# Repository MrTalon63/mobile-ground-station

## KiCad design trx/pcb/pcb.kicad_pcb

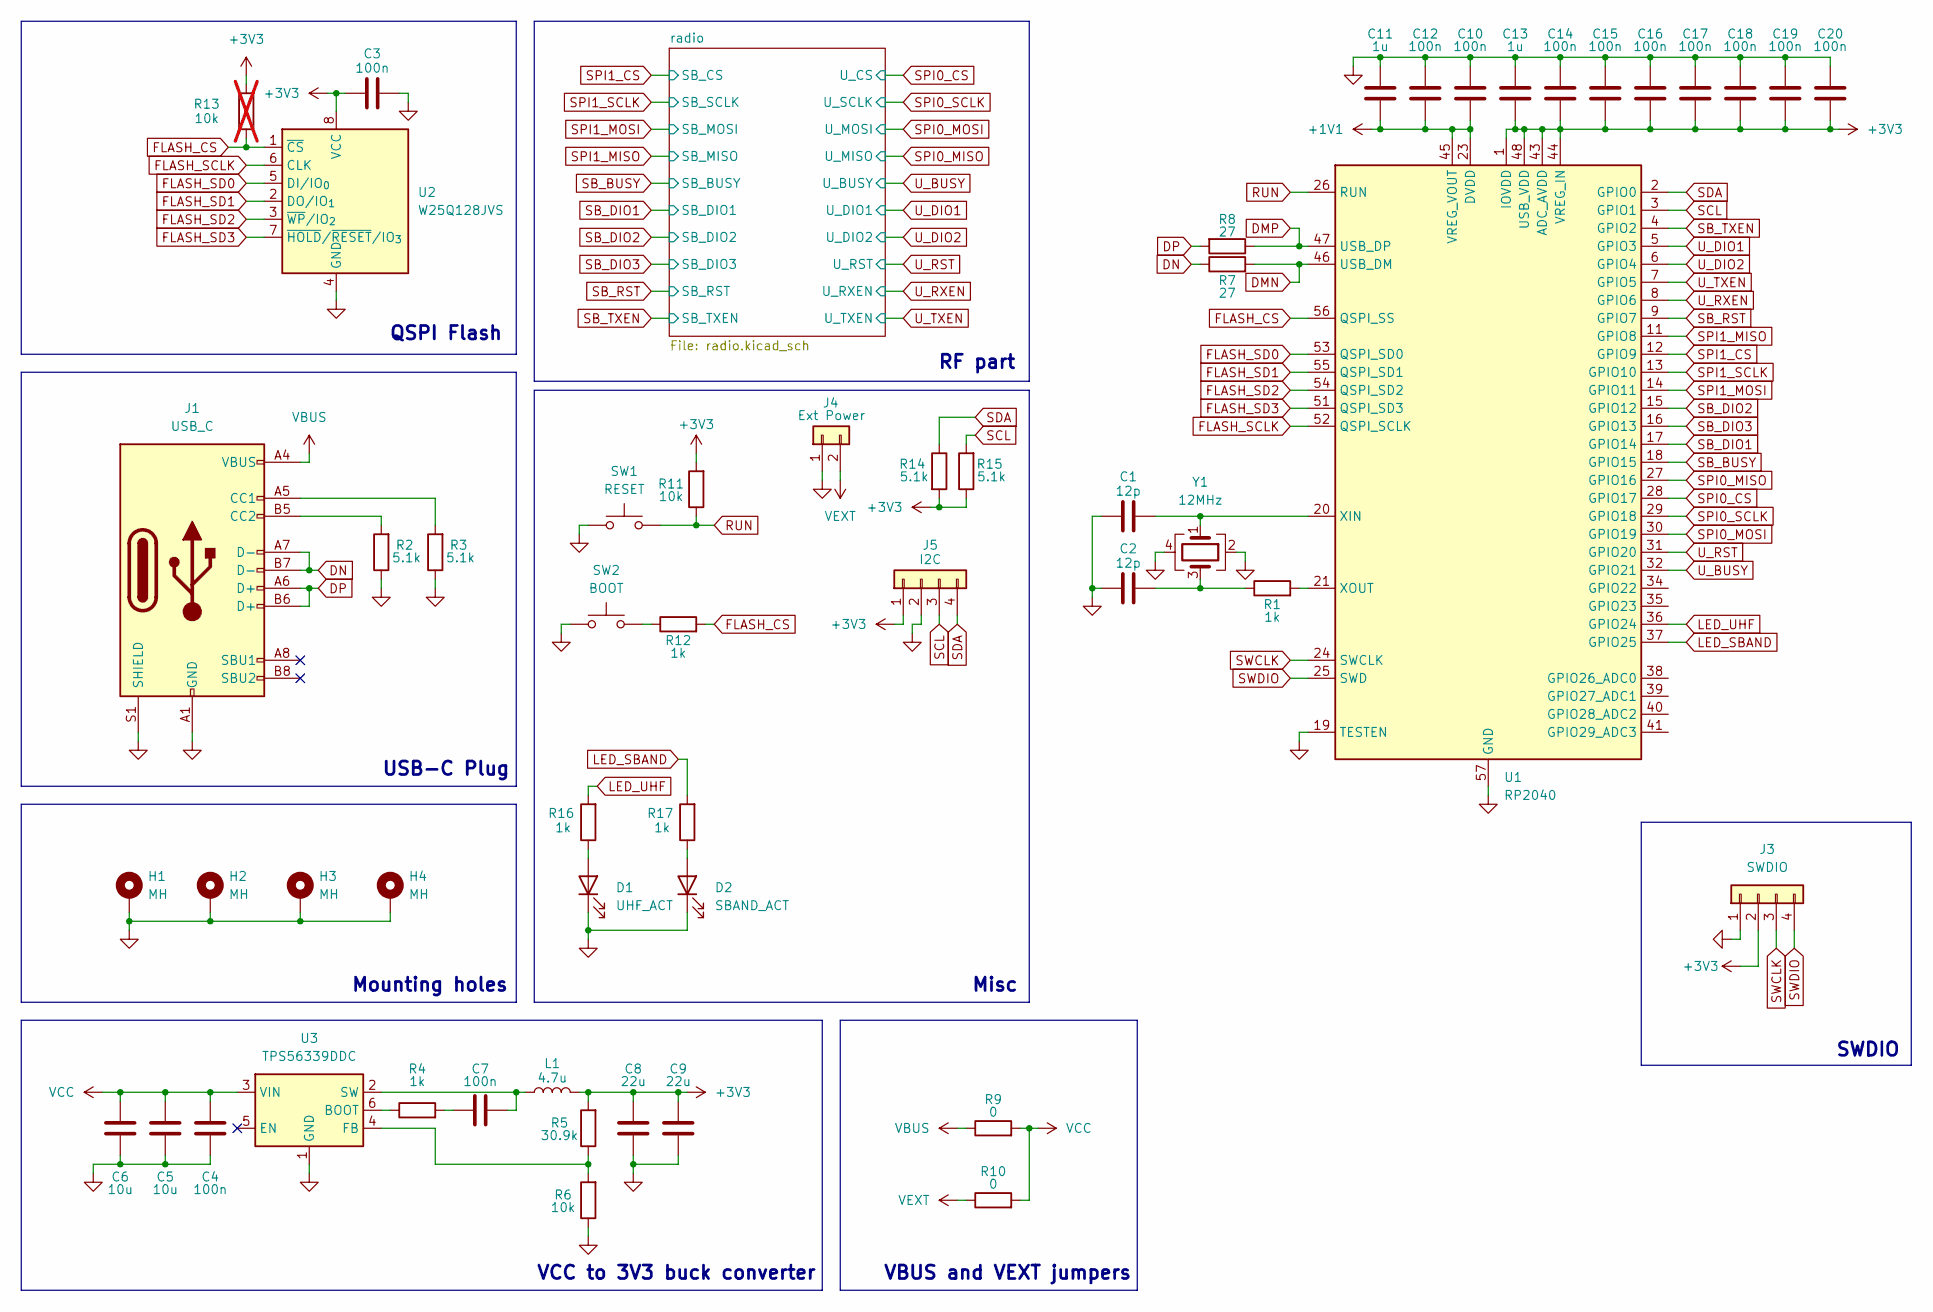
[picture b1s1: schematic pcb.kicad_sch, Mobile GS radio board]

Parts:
C1, C2: 12p; C_0603_1608Metric_Pad1.08x0.95mm_HandSolder
C3, C4, C7, C10, C12, C14, C15, C16, C17, C18, C19, C20: 100n; C_0603_1608Metric_Pad1.08x0.95mm_HandSolder
C5, C6: 10u; C_0603_1608Metric_Pad1.08x0.95mm_HandSolder
C8, C9: 22u; C_0603_1608Metric_Pad1.08x0.95mm_HandSolder
C11, C13: 1u; C_0603_1608Metric_Pad1.08x0.95mm_HandSolder
D1: UHF_ACT; LED_0805_2012Metric_Pad1.15x1.40mm_HandSolder
D2: SBAND_ACT; LED_0805_2012Metric_Pad1.15x1.40mm_HandSolder
H1, H2, H3, H4: MH; MountingHole_2.7mm_M2.5_Pad
J1: USB_C; USB_C_Receptacle_GCT_USB4105-xx-A_16P_TopMnt_Horizontal
J3: SWDIO; PinHeader_1x04_P2.54mm_Vertical
J4: Ext Power; PinSocket_1x02_P2.54mm_Vertical
J5: I2C; PinHeader_1x04_P2.54mm_Vertical
L1: 4.7u; L_Vishay_IHLP-2525
R1, R4, R12, R16, R17: 1k; R_0603_1608Metric_Pad0.98x0.95mm_HandSolder
R2, R3, R14, R15: 5.1k; R_0603_1608Metric_Pad0.98x0.95mm_HandSolder
R5: 30.9k; R_0603_1608Metric_Pad0.98x0.95mm_HandSolder
R6, R11: 10k; R_0603_1608Metric_Pad0.98x0.95mm_HandSolder
R7, R8: 27; R_0603_1608Metric_Pad0.98x0.95mm_HandSolder
R9, R10: 0; R_0805_2012Metric_Pad1.20x1.40mm_HandSolder
R13: 10k; R_0603_1608Metric_Pad0.98x0.95mm_HandSolder; not fitted
SW1: RESET; SW_Push_1P1T_NO_CK_KSC6xxJ
SW2: BOOT; SW_Push_1P1T_NO_CK_KSC6xxJ
U1: RP2040; QFN-56-1EP_7x7mm_P0.4mm_EP3.2x3.2mm
U2: W25Q128JVS; SOIC-8_5.3x5.3mm_P1.27mm
U3: TPS56339DDC; SOT-23-6
Y1: 12MHz; Crystal_SMD_Abracon_ABM3B-4Pin_5.0x3.2mm

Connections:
+1V1: C10.2, C11.2, C12.2, U1.23 (DVDD), U1.45 (VREG_VOUT), U1.50 (DVDD)
+3V3: C3.1, C8.2, C9.2, C13.2, C14.2, C15.2, C16.2, C17.2, C18.2, C19.2, C20.2, J3.2, J5.1, L1.2, R5.2, R11.2, R13.2, R14.2, R15.1, U1.1 (IOVDD), U1.10 (IOVDD), U1.22 (IOVDD), U1.33 (IOVDD), U1.42 (IOVDD), U1.43 (ADC_AVDD), U1.44 (VREG_IN), U1.48 (USB_VDD), U1.49 (IOVDD), U2.8 (VCC); also elsewhere on the board
DMN: R7.2, U1.46 (USB_DM)
DMP: R8.1, U1.47 (USB_DP)
DN: J1.A7 (D-), J1.B7 (D-), R7.1
DP: J1.A6 (D+), J1.B6 (D+), R8.2
FLASH_CS: R12.2, R13.1, U1.56 (QSPI_SS), U2.1 (~CS)
FLASH_SCLK: U1.52 (QSPI_SCLK), U2.6 (CLK)
FLASH_SD0: U1.53 (QSPI_SD0), U2.5 (DI/IO_{0})
FLASH_SD1: U1.55 (QSPI_SD1), U2.2 (DO/IO_{1})
FLASH_SD2: U1.54 (QSPI_SD2), U2.3 (~WP/IO_{2})
FLASH_SD3: U1.51 (QSPI_SD3), U2.7 (~HOLD/~RESET/IO_{3})
GND: C1.1, C2.1, C3.2, C4.1, C5.1, C6.1, C8.1, C9.1, C10.1, C11.1, C12.1, C13.1, C14.1, C15.1, C16.1, C17.1, C18.1, C19.1, C20.1, D1.1 (K), D2.1 (K), H1.1, H2.1, H3.1, H4.1, J1.A1 (GND), J1.A12 (GND), J1.B1 (GND), J1.B12 (GND), J1.S1 (SHIELD), J3.1, J4.1, J5.2, R2.1, R3.1, R6.1, SW1.1, SW2.1, U1.19 (TESTEN), U1.57 (GND), U2.4 (GND), U3.1 (GND), Y1.2, Y1.4; also elsewhere on the board
LED_SBAND: R17.2, U1.37 (GPIO25)
LED_UHF: R16.2, U1.36 (GPIO24)
unnamed: C2.2, R1.1, Y1.3
unnamed: C7.2, R4.2
unnamed: D1.2 (A), R16.1
unnamed: D2.2 (A), R17.1
unnamed: J1.A5 (CC1), R3.2
unnamed: J1.B5 (CC2), R2.2
unnamed: R12.1, SW2.2
unnamed: C1.2, U1.20 (XIN), Y1.1
unnamed: R1.2, U1.21 (XOUT)
unnamed: R4.1, U3.6 (BOOT)
unnamed: R5.1, R6.2, U3.4 (FB)
unnamed: C7.1, L1.1, U3.2 (SW)
RUN: R11.1, SW1.2, U1.26 (RUN)
SB_BUSY: U1.18 (GPIO15); also elsewhere on the board
SB_DIO1: U1.17 (GPIO14); also elsewhere on the board
SB_DIO2: U1.15 (GPIO12); also elsewhere on the board
SB_DIO3: U1.16 (GPIO13); also elsewhere on the board
SB_RST: U1.9 (GPIO7); also elsewhere on the board
SB_TXEN: U1.4 (GPIO2); also elsewhere on the board
SCL: J5.3, R15.2, U1.3 (GPIO1)
SDA: J5.4, R14.1, U1.2 (GPIO0)
SPI0_CS: U1.28 (GPIO17); also elsewhere on the board
SPI0_MISO: U1.27 (GPIO16); also elsewhere on the board
SPI0_MOSI: U1.30 (GPIO19); also elsewhere on the board
SPI0_SCLK: U1.29 (GPIO18); also elsewhere on the board
SPI1_CS: U1.12 (GPIO9); also elsewhere on the board
SPI1_MISO: U1.11 (GPIO8); also elsewhere on the board
SPI1_MOSI: U1.14 (GPIO11); also elsewhere on the board
SPI1_SCLK: U1.13 (GPIO10); also elsewhere on the board
SWCLK: J3.3, U1.24 (SWCLK)
SWDIO: J3.4, U1.25 (SWD)
U_BUSY: U1.32 (GPIO21); also elsewhere on the board
U_DIO1: U1.5 (GPIO3); also elsewhere on the board
U_DIO2: U1.6 (GPIO4); also elsewhere on the board
U_RST: U1.31 (GPIO20); also elsewhere on the board
U_RXEN: U1.8 (GPIO6); also elsewhere on the board
U_TXEN: U1.7 (GPIO5); also elsewhere on the board
VBUS: J1.A4 (VBUS), J1.A9 (VBUS), J1.B4 (VBUS), J1.B9 (VBUS), R9.1
VCC: C4.2, C5.2, C6.2, R9.2, R10.2, U3.3 (VIN)
VEXT: J4.2, R10.1

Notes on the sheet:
QSPI Flash
Misc
VBUS and VEXT jumpers
RF part
Mounting holes
USB-C Plug
SWDIO
VCC to 3V3 buck converter

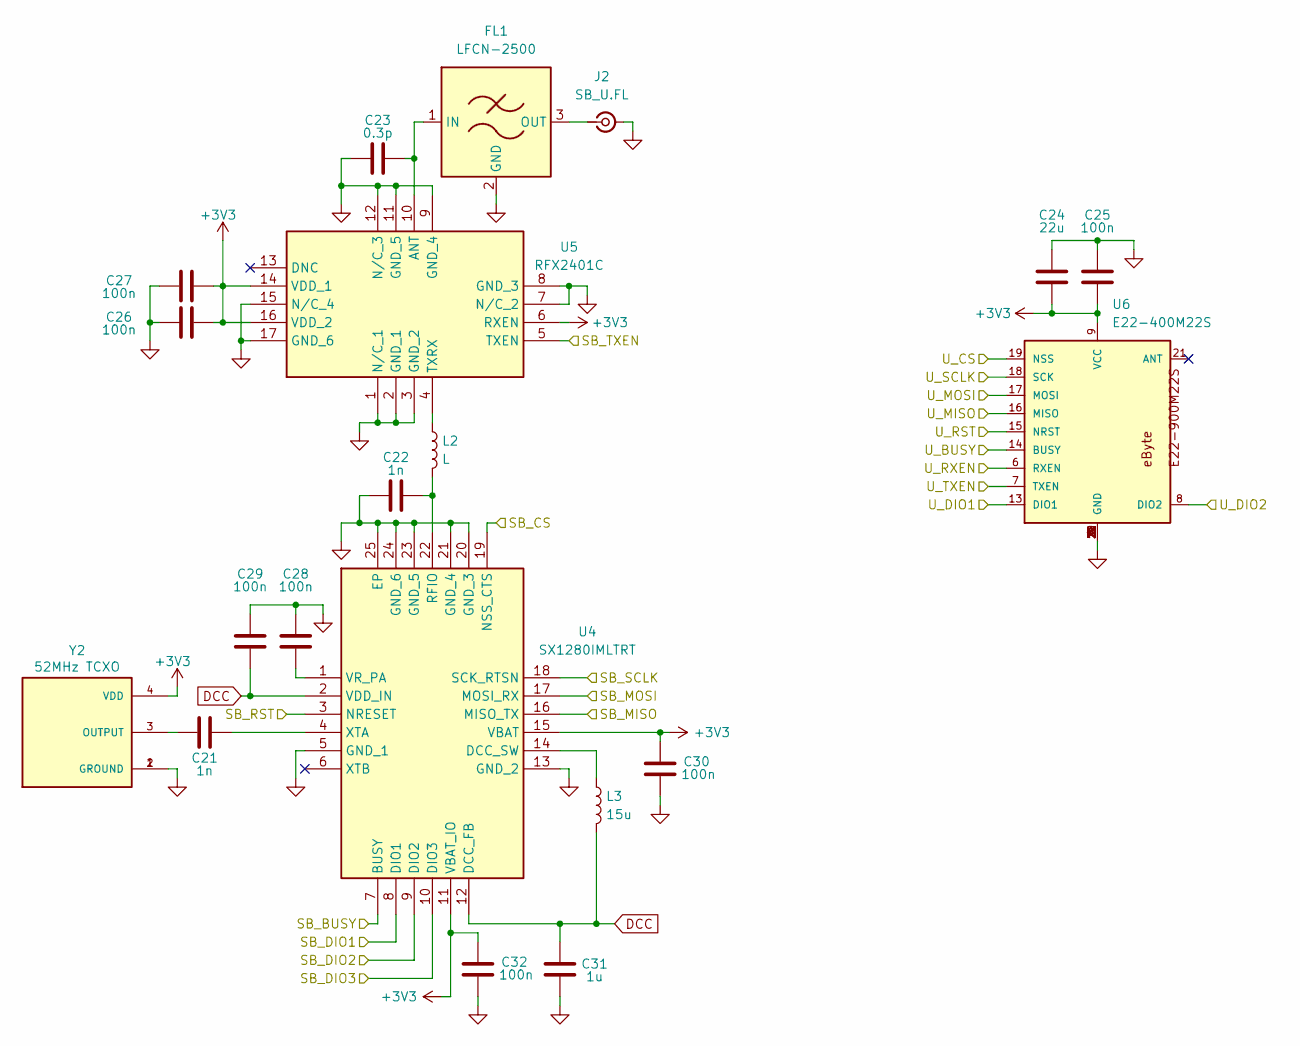
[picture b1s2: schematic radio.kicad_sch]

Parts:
C21: 1n; C_0603_1608Metric_Pad1.08x0.95mm_HandSolder
C22: 1n; C_0402_1005Metric_Pad0.74x0.62mm_HandSolder
C23: 0.3p; C_0603_1608Metric_Pad1.08x0.95mm_HandSolder
C24: 22u; C_0603_1608Metric_Pad1.08x0.95mm_HandSolder
C25, C26, C27, C28, C29, C30, C32: 100n; C_0603_1608Metric_Pad1.08x0.95mm_HandSolder
C31: 1u; C_0603_1608Metric_Pad1.08x0.95mm_HandSolder
FL1: LFCN-2500; Filter_Mini-Circuits_FV1206
J2: SB_U.FL; U.FL_Molex_MCRF_73412-0110_Vertical
L2: L; L_0402_1005Metric_Pad0.77x0.64mm_HandSolder
L3: 15u; L_0805_2012Metric_Pad1.15x1.40mm_HandSolder
U4: SX1280IMLTRT; QFN50P400X400X100-25N-D; Mouser Part Number 947-SX1280IMLTRT
U5: RFX2401C; QFN50P300X300X60-17N-D; Mouser Part Number 477-RFX2401C
U6: E22-400M22S; E22-900M22S
Y2: 52MHz TCXO; OSC_ECS-TXO-20CSMV4-520-AN-TR

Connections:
+3V3: C24.1, C25.2, C26.1, C27.1, C30.1, C32.1, U4.11 (VBAT_IO), U4.15 (VBAT), U5.6 (RXEN), U5.14 (VDD_1), U5.16 (VDD_2), U6.9 (VCC), Y2.4 (VDD); also elsewhere on the board
DCC: C29.2, C31.1, L3.2, U4.2 (VDD_IN), U4.12 (DCC_FB)
GND: C22.2, C23.2, C24.2, C25.1, C26.2, C27.2, C28.1, C29.1, C30.2, C31.2, C32.2, FL1.2 (GND), FL1.4 (GND), J2.2 (Ext), U4.5 (GND_1), U4.13 (GND_2), U4.20 (GND_3), U4.21 (GND_4), U4.23 (GND_5), U4.24 (GND_6), U4.25 (EP), U5.1 (N/C_1), U5.2 (GND_1), U5.3 (GND_2), U5.7 (N/C_2), U5.8 (GND_3), U5.9 (GND_4), U5.11 (GND_5), U5.12 (N/C_3), U5.15 (N/C_4), U5.17 (GND_6), U6.1 (GND), U6.2 (GND), U6.3 (GND), U6.4 (GND), U6.5 (GND), U6.10 (GND), U6.11 (GND), U6.12 (GND), U6.20 (GND), U6.22 (GND), Y2.1 (GROUND), Y2.2 (GROUND); also elsewhere on the board
unnamed: C23.1, FL1.1 (IN), U5.10 (ANT)
unnamed: FL1.3 (OUT), J2.1 (In)
unnamed: L3.1, U4.14 (DCC_SW)
unnamed: C22.1, L2.2, U4.22 (RFIO)
unnamed: C28.2, U4.1 (VR_PA)
unnamed: C21.1, U4.4 (XTA)
unnamed: L2.1, U5.4 (TXRX)
unnamed: C21.2, Y2.3 (OUTPUT)
SB_BUSY: U4.7 (BUSY); also elsewhere on the board
SB_DIO1: U4.8 (DIO1); also elsewhere on the board
SB_DIO2: U4.9 (DIO2); also elsewhere on the board
SB_DIO3: U4.10 (DIO3); also elsewhere on the board
SB_RST: U4.3 (NRESET); also elsewhere on the board
SB_TXEN: U5.5 (TXEN); also elsewhere on the board
SPI0_CS: U6.19 (NSS); also elsewhere on the board
SPI0_MISO: U6.16 (MISO); also elsewhere on the board
SPI0_MOSI: U6.17 (MOSI); also elsewhere on the board
SPI0_SCLK: U6.18 (SCK); also elsewhere on the board
SPI1_CS: U4.19 (NSS_CTS); also elsewhere on the board
SPI1_MISO: U4.16 (MISO_TX); also elsewhere on the board
SPI1_MOSI: U4.17 (MOSI_RX); also elsewhere on the board
SPI1_SCLK: U4.18 (SCK_RTSN); also elsewhere on the board
U_BUSY: U6.14 (BUSY); also elsewhere on the board
U_DIO1: U6.13 (DIO1); also elsewhere on the board
U_DIO2: U6.8 (DIO2); also elsewhere on the board
U_RST: U6.15 (NRST); also elsewhere on the board
U_RXEN: U6.6 (RXEN); also elsewhere on the board
U_TXEN: U6.7 (TXEN); also elsewhere on the board

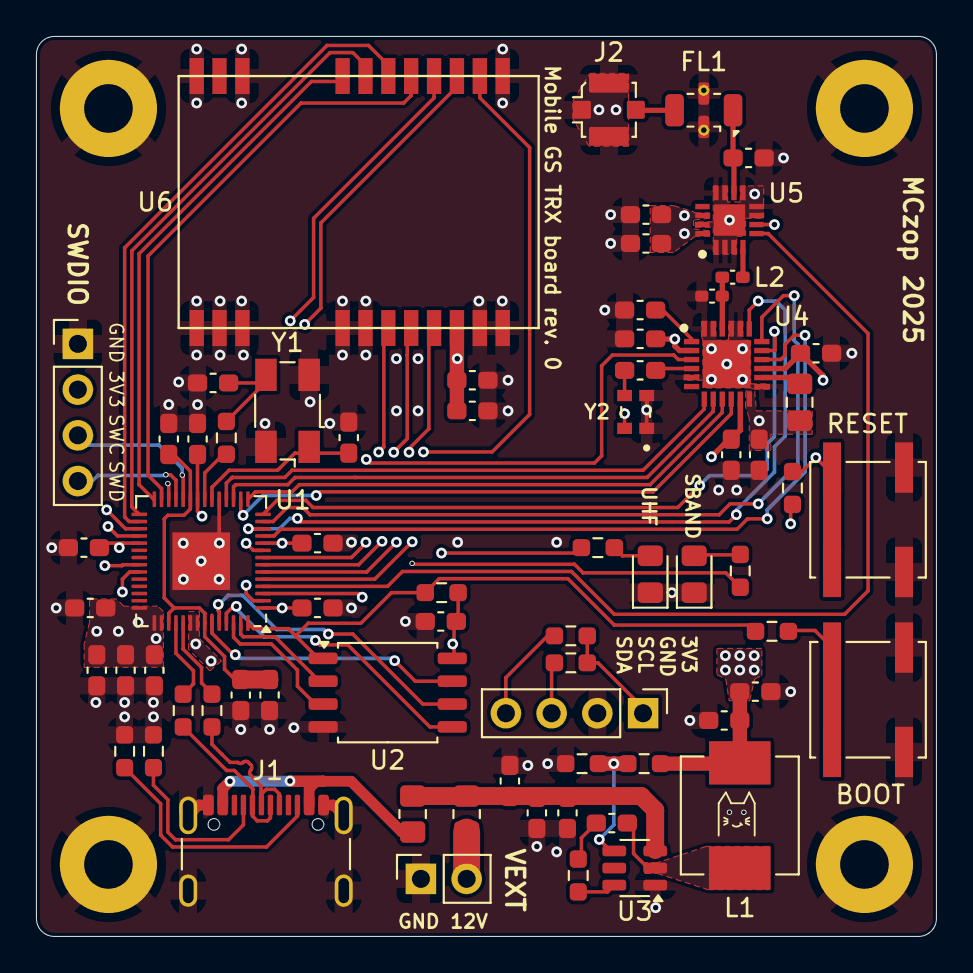
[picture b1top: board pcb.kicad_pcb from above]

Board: 4 copper layers, 50.0 x 50.0 mm, 74 parts (0 on the bottom side), 64 nets.

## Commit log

2025-05-08 initial uC design
2025-05-13 Update design
2025-05-13 Update designators
